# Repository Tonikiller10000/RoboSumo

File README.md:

# RoboSumo

## Description:

This is a SUMO robot for comperitions. It pushes the opponent\`s robot out of the ring.
    
It uses:
- ATmega328p-AU as an microcontroller(used in arduino uno);
- 16 or 20Mhz crystal resonator;
- [TB6612FNG](https://github.com/Tonikiller10000/MotorDriver_1) DC motor driver;
- [VL53L0x](https://github.com/Tonikiller10000/VL53L0x_DistanceSensor) distance sensor;
- LI-PO battery (7.2V)
- 2x DC motors with low torque high speed gear box
- robot suport (Wood, 3d printed or any low weight matherial)

<table>
  <tr>
    <td></td>
    <td></td>
    <td></td>
  </tr>
</table>

Schematic:

### How it works:
The board is like a custom arduino UNO board powered from an 7.2V Li-Po battery trouth an 5V voltage regulator. 6 digital pins are used for the TB6612FNG motor driver witch is powered dirrectly from the battery to give more power to the motors. The reset pin has a 10K pullup resistor witch is pulled down by the reset button when it is pressed. The UART and ICSP pins wore pulled out to program the code and the bootloader of the IC.
For now I will try to use the [VL53L0x](https://github.com/Tonikiller10000/VL53L0x_DistanceSensor) I2C distance sensor, because [other sensors](https://github.com/Tonikiller10000/RoboSumo/blob/main/PozeRoboSumo/s1.png) are a little to slow.

### Programming:
Programming of the robot is done via UART protocoll with an [FTDI](https://github.com/Tonikiller10000/CH340G-FTDI-PROGRAMER) programming board. The code for the RoboSumo is not ready. 
 
### Design and mentions

This is The model I followed and some tips:
- to reach better torque on the wheels, it should be wider. 
- to mount the motors use molderd plastic motor holders, or be carefull when printing [it](https://github.com/Tonikiller10000/LineFollower/blob/main/LineFollower_Pictures/w1.jpg). 
- the case was made with autodesk fusion 360 at the 3d printer and with some M3 screws.

<table>
  <tr>
    <td></td>
    <td></td>
    <td></td>
  </tr>
</table>

The next version will have the motor driver soldered on the board and motors screwed dirrectly to it as the suport. Also I will try to make a smaller version

## Links: 
- ATmega328p-AU (microcontroller): 
- LM78L05 (5V voltage regulator):

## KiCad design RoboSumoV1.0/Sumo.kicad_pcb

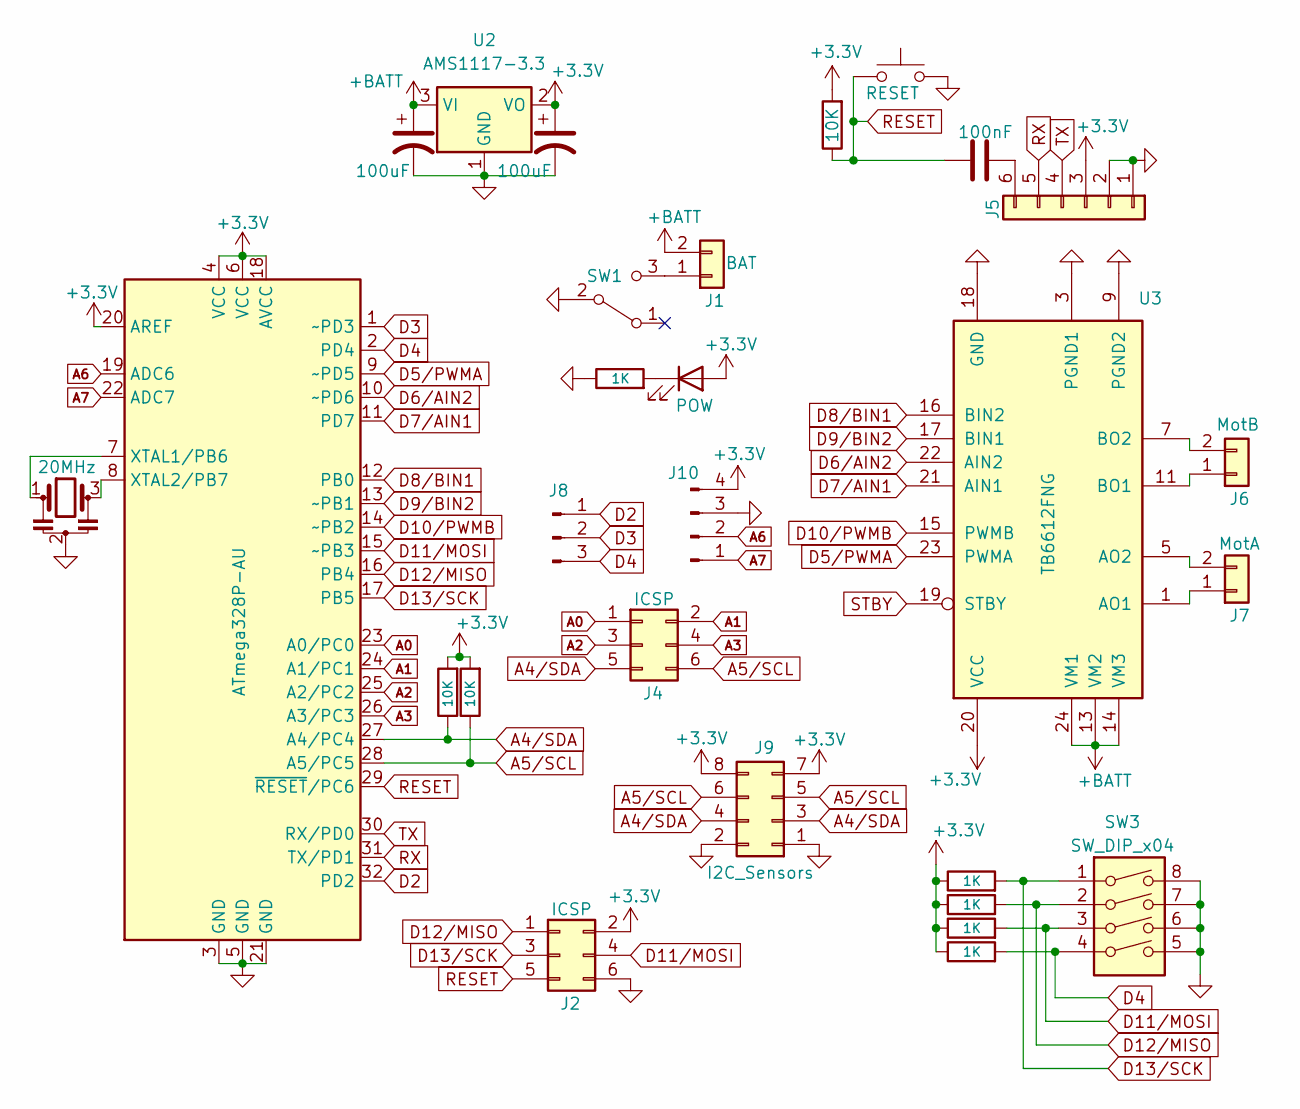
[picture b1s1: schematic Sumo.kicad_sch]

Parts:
C1, C2: 100uF; C_1210_3225Metric_Pad1.33x2.70mm_HandSolder
C3: 100nF; C_0805_2012Metric
D1: POW
J1: BAT; PinHeader_1x02_P2.54mm_Vertical
J2, J4: ICSP; PinHeader_2x03_P2.54mm_Vertical
J5: Conn_01x06_MountingPin
J6: MotB; PinHeader_1x02_P2.54mm_Horizontal
J7: MotA; PinHeader_1x02_P2.54mm_Horizontal
J8: Conn_01x03_Pin
J9: I2C_Sensors
J10: Conn_01x04_Pin
R1, R7, R8, R9, R10: 1K; R_1206_3216Metric
R2, R11, R12: 10K; R_1206_3216Metric
SW1: SW_SPDT
SW2: RESET
SW3: SW_DIP_x04
U1: ATmega328P-AU; TQFP-32_7x7mm_P0.8mm
U2: AMS1117-3.3; SOT-223-3_TabPin2
U3: TB6612FNG; SSOP-24_5.3x8.2mm_P0.65mm
Y1: 20MHz; Resonator_SMD_Murata_CSTxExxV-3Pin_3.0x1.1mm

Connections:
+5V: C2.1, D1.2 (A), J2.2, J5.3, J9.7, J9.8, J10.4, R2.2, R7.1, R8.1, R9.1, R10.1, R11.2, R12.2, U1.4 (VCC), U1.6 (VCC), U1.18 (AVCC), U1.20 (AREF), U2.2 (VO); also elsewhere on the board
+BATT: C1.1, J1.2, U2.3 (VI); also elsewhere on the board
A0: J4.1, U1.23 (A0/PC0)
A1: J4.2, U1.24 (A1/PC1)
A2: J4.3, U1.25 (A2/PC2)
A3: J4.4, U1.26 (A3/PC3)
A4/SDA: J4.5, J9.3, J9.4, R11.1, U1.27 (A4/PC4)
A5/SCL: J4.6, J9.5, J9.6, R12.1, U1.28 (A5/PC5)
A6: J10.2, U1.19 (ADC6)
A7: J10.1, U1.22 (ADC7)
D2: J8.1, U1.32 (PD2)
D3: J8.2, U1.1 (~PD3)
D4: J8.3, R10.2, SW3.4, U1.2 (PD4)
D5/PWMA: U1.9 (~PD5), U3.23 (PWMA); also elsewhere on the board
D6/AIN2: U1.10 (~PD6), U3.22 (AIN2); also elsewhere on the board
D7/AIN1: U1.11 (PD7), U3.21 (AIN1); also elsewhere on the board
D8/BIN1: U1.12 (PB0), U3.16 (BIN2); also elsewhere on the board
D9/BIN2: U1.13 (~PB1), U3.17 (BIN1); also elsewhere on the board
D10/PWMB: U1.14 (~PB2), U3.15 (PWMB); also elsewhere on the board
D11/MOSI: J2.4, R9.2, SW3.3, U1.15 (~PB3)
D12/MISO: J2.1, R8.2, SW3.2, U1.16 (PB4)
D13/SCK: J2.3, R7.2, SW3.1, U1.17 (PB5)
GND: C1.2, C2.2, J2.6, J5.1, J5.2, J9.1, J9.2, J10.3, R1.1, SW1.2 (B), SW2.1, SW3.5, SW3.6, SW3.7, SW3.8, U1.3 (GND), U1.5 (GND), U1.21 (GND), U2.1 (GND), Y1.2; also elsewhere on the board
unnamed: D1.1 (K), R1.2
unnamed: J1.1, SW1.3 (C)
unnamed: C3.1, J5.6
unnamed 26: J6.1; also elsewhere on the board
unnamed 27: J6.2; also elsewhere on the board
unnamed 28: J7.1; also elsewhere on the board
unnamed 29: J7.2; also elsewhere on the board
unnamed: U1.7 (XTAL1/PB6), Y1.1
unnamed: U1.8 (XTAL2/PB7), Y1.3
RESET: C3.2, J2.5, R2.1, SW2.2, U1.29 (~RESET/PC6)
RX: J5.5, U1.31 (TX/PD1)
TX: J5.4, U1.30 (RX/PD0)

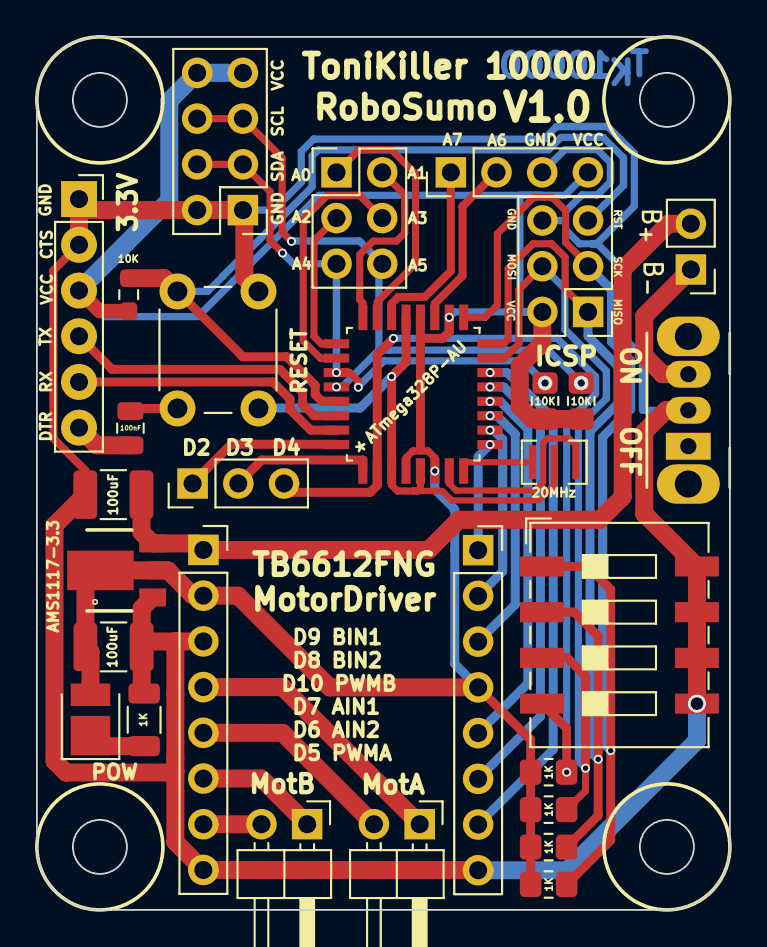
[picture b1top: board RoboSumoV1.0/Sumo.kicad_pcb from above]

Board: 2 copper layers, 38.5 x 48.5 mm, 29 parts (0 on the bottom side), 35 nets.

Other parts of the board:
J20: BAT; PinSocket_1x08_P2.54mm_Vertical
J21: Conn_01x03; PinSocket_1x08_P2.54mm_Vertical

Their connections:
+5V: J20.2, J21.4; also elsewhere on the board
+BATT: J20.1; also elsewhere on the board
D5/PWMA: J21.1; also elsewhere on the board
D6/AIN2: J21.2; also elsewhere on the board
D7/AIN1: J21.3; also elsewhere on the board
D8/BIN1: J21.5; also elsewhere on the board
D9/BIN2: J21.6; also elsewhere on the board
D10/PWMB: J21.7; also elsewhere on the board
GND: J20.3, J20.8, J21.8; also elsewhere on the board
unnamed 26: J20.6; also elsewhere on the board
unnamed 27: J20.7; also elsewhere on the board
unnamed 28: J20.4; also elsewhere on the board
unnamed 29: J20.5; also elsewhere on the board

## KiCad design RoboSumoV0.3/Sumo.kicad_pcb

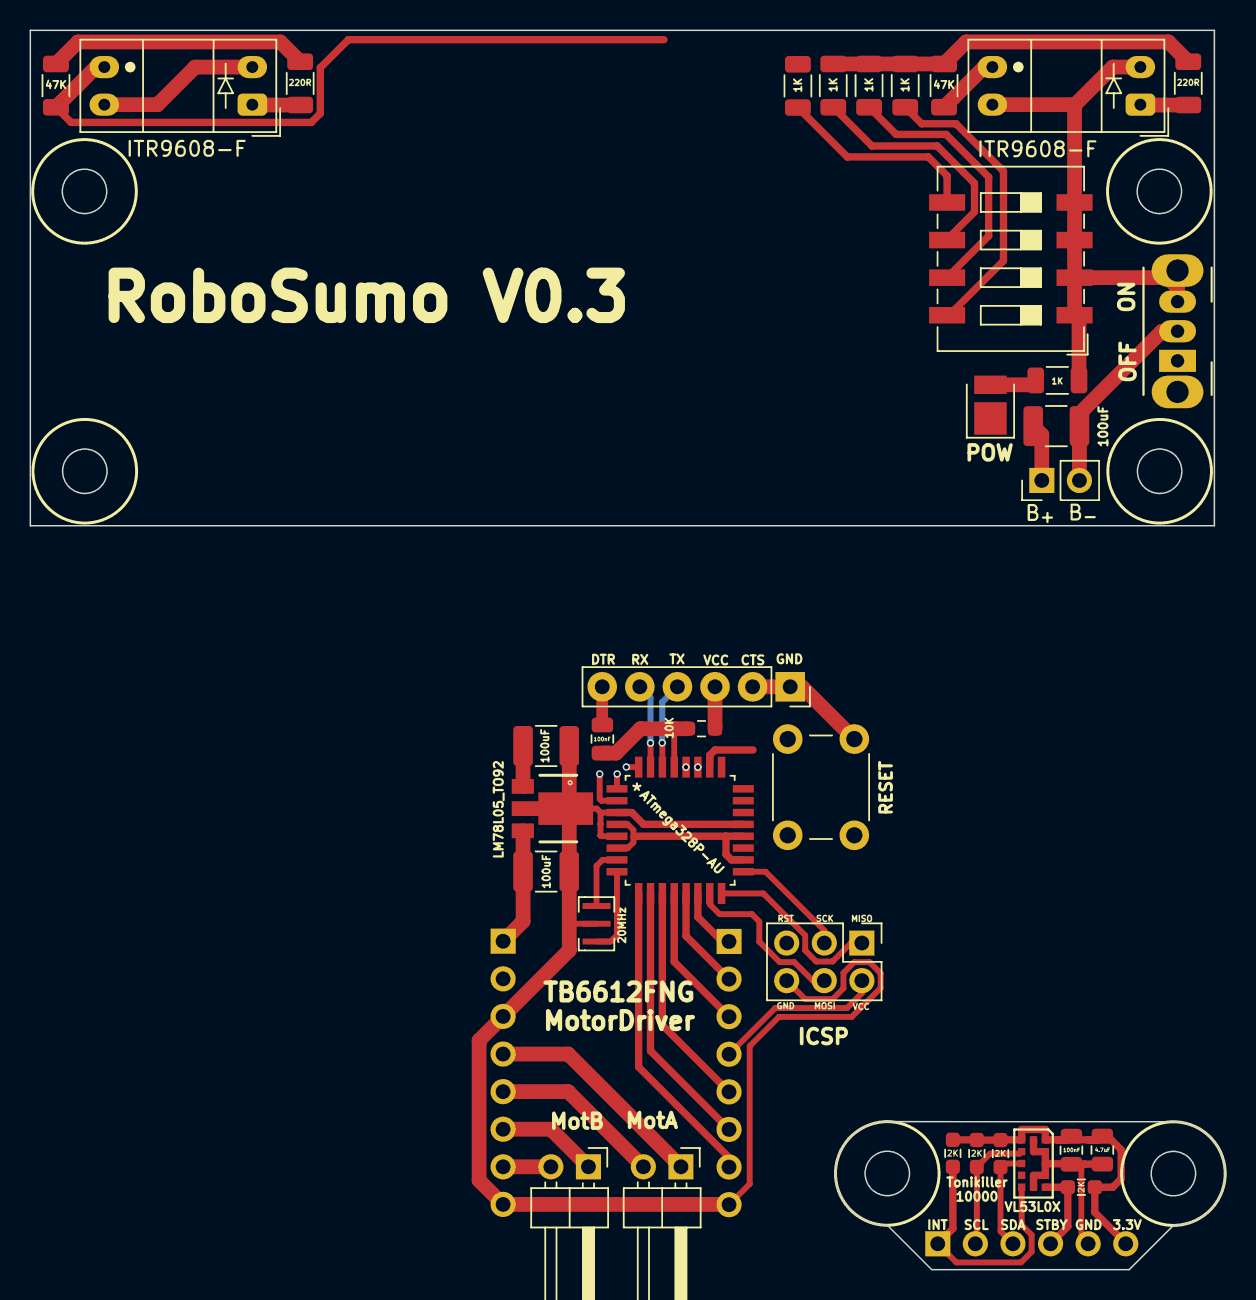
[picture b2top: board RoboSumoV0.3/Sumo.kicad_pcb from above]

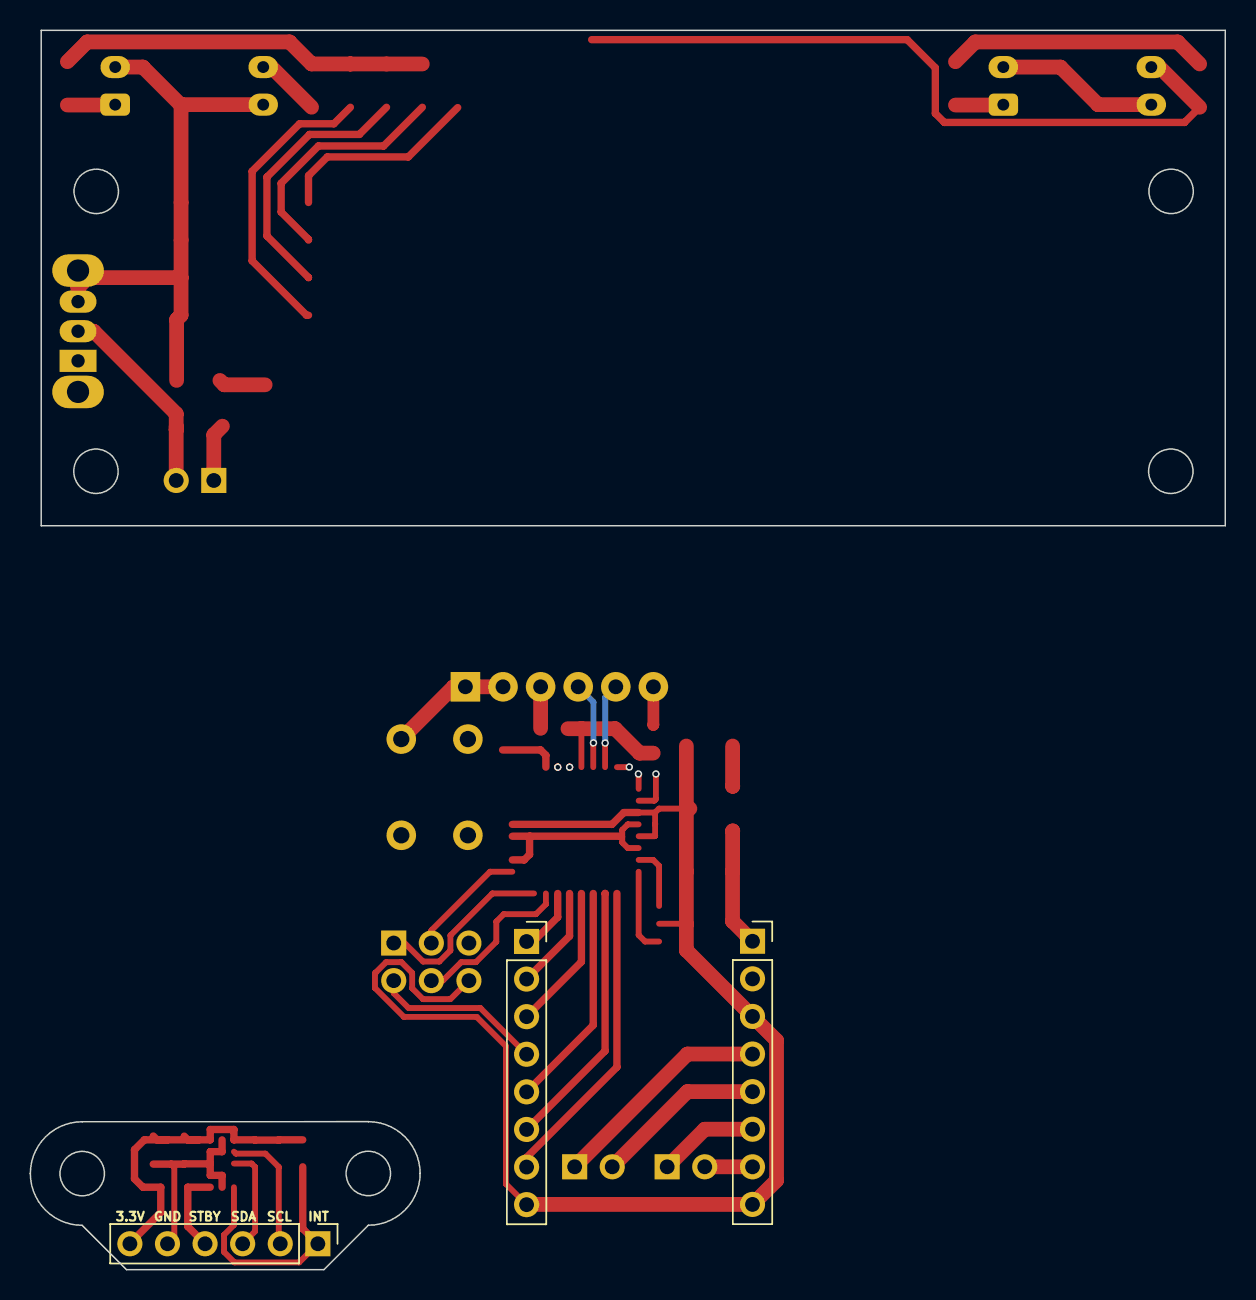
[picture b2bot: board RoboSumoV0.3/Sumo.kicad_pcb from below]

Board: 2 copper layers, 80.7 x 83.7 mm, 35 parts (2 on the bottom side), 27 nets.

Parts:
C1, C1#2, C2: 100uF; C_1210_3225Metric_Pad1.33x2.70mm_HandSolder
C3, C3#2: 100nF; C_0805_2012Metric
C3#3: 4.7uF; C_0805_2012Metric
D1: POW; LED_PLCC_2835
J1: BAT; PinHeader_1x02_P2.54mm_Vertical
J2: ICSP; PinHeader_2x03_P2.54mm_Vertical
J4: Conn_01x06_MountingPin; PinSocket_1x06_P2.54mm_Vertical
J6: MotB; PinHeader_1x02_P2.54mm_Horizontal
J7: MotA; PinHeader_1x02_P2.54mm_Horizontal
J8: BAT; PinSocket_1x08_P2.54mm_Vertical
J9: Conn_01x03; PinSocket_1x08_P2.54mm_Vertical
R1: 10K; R_0603_1608Metric_Pad0.98x0.95mm_HandSolder
R1#2, R1#3, R1#4, R1#5: 2K; R_0603_1608Metric_Pad0.98x0.95mm_HandSolder
R2, R20, R20#2, R20#3, R20#4: 1K; R_1206_3216Metric
R3, R5: 220R; R_1206_3216Metric
R4, R6: 47K; R_1206_3216Metric
SW1: RESET; SW_CuK_OS102011MA1QN1_SPDT_Angled
SW2: RESET; SW_PUSH_6mm
U1: ATmega328P-AU; TQFP32_32A_MCH
U2: LM78L05_TO92; PK(R-PSSO-F3)
U4, U5: ITR9608-F; Everlight_ITR9608-F
Y1: 20MHz; Resonator_SMD_Murata_CSTxExxV-3Pin_3.0x1.1mm

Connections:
0V: C1#2.2, C2.2, D1.1 (K), J2.6, J4.1, J4.2, J8.3, J8.8, J9.8, R2.2, SW1.3, SW2.2, U1.3 (GND), U1.5 (GND), U1.21 (GND), U2.2 (GND), U4.2, U4.4, U5.2, U5.4, Y1.2
5V: C2.1, J2.2, J4.3, J9.4, R3.2, R4.1, R5.2, R6.1, R20.1, R20#2.1, R20#3.1, R20#4.1, U1.4 (VCC), U1.6 (VCC), U1.18 (AVCC), U1.20 (AREF), U2.1 (VO)
+BATT: C1.1, C1#2.1, J1.1, J8.1, U2.3 (VI)
AIN1: J9.3, U1.12 (PB0), U1.32 (PD2)
AIN2: J9.2, U1.2 (PD4), U1.13 (~PB1)
BIN1: J9.5, U1.11 (PD7)
BIN2: J9.6, U1.10 (~PD6)
MISO: J2.1, U1.16 (PB4)
MOSI: J2.4, U1.15 (~PB3)
unnamed: D1.2 (A), R2.1
unnamed: C1.2, J1.2, SW1.2
unnamed: J6.1, J8.6
unnamed: J6.x (Pin_2), J8.7
unnamed: J7.1, J8.4
unnamed: J7.2, J8.5
unnamed: R3.1, U4.1
unnamed: R5.1, U5.1
unnamed: U1.7 (XTAL1/PB6), Y1.1
unnamed: U1.8 (XTAL2/PB7), Y1.3
PWMA: J9.1, U1.1 (~PD3), U1.14 (~PB2)
PWMB: J9.7, U1.9 (~PD5)
RESET: C3.2, J2.5, R1.1, SW2.1, U1.29 (~RESET/PC6)
RX: J4.5, U1.31 (TX/PD1)
SCK: J2.3, U1.17 (PB5)
Sensor4: R6.2, U1.27 (A4/PC4), U5.3
Sensor5: R4.2, U1.28 (A5/PC5), U4.3
TX: J4.4, U1.30 (RX/PD0)

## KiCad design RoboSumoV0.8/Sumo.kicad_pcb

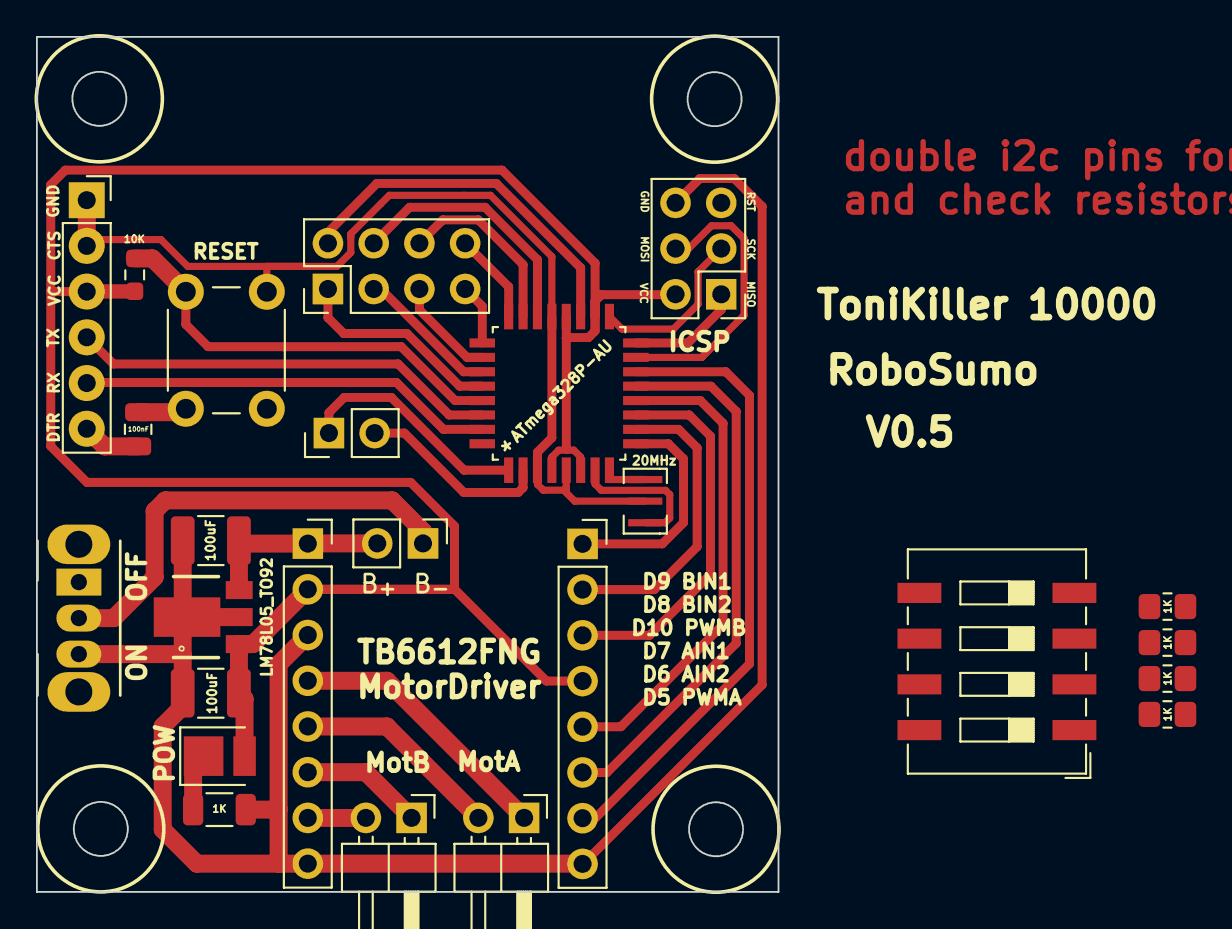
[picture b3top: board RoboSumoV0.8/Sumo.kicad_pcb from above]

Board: 2 copper layers, 41.2 x 47.5 mm, 24 parts (0 on the bottom side), 27 nets.

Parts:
C1, C2: 100uF; C_1210_3225Metric_Pad1.33x2.70mm_HandSolder
C3: 100nF; C_0805_2012Metric
D1: POW; LED_PLCC_2835
J1, J1#2: BAT; PinHeader_1x02_P2.54mm_Vertical
J2: ICSP; PinHeader_2x03_P2.54mm_Vertical
J5: Conn_01x06_MountingPin; PinSocket_1x06_P2.54mm_Vertical
J6: MotB; PinHeader_1x02_P2.54mm_Horizontal
J7: MotA; PinHeader_1x02_P2.54mm_Horizontal
J8: BAT; PinSocket_1x08_P2.54mm_Vertical
J9: Conn_01x03; PinSocket_1x08_P2.54mm_Vertical
R1: 1K; R_1206_3216Metric
R2: 10K; R_0603_1608Metric_Pad0.98x0.95mm_HandSolder
R7, R8, R9, R10: 1K; R_0805_2012Metric_Pad1.20x1.40mm_HandSolder
SW1: SW_SPDT; SW_CuK_OS102011MA1QN1_SPDT_Angled
SW2: RESET; SW_PUSH_6mm
SW3: SW_DIP_x04; SW_DIP_SPSTx04_Slide_9.78x12.34mm_W8.61mm_P2.54mm
U1: ATmega328P-AU; TQFP32_32A_MCH
U2: LM78L05_TO92; PK(R-PSSO-F3)
Y1: 20MHz; Resonator_SMD_Murata_CSTxExxV-3Pin_3.0x1.1mm

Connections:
+5V: C2.1, D1.2 (A), J2.2, J5.3, J8.2, J9.4, R2.2, R7.1, R8.1, R9.1, R10.1, U1.4 (VCC), U1.6 (VCC), U1.18 (AVCC), U1.20 (AREF), U2.1 (VO)
+BATT: C1.1, J1#2.2, J8.1, U2.3 (VI)
AIN1: J9.3, U1.11 (PD7)
AIN2: J9.2, U1.10 (~PD6)
BIN1: J9.5, U1.12 (PB0)
BIN2: J9.6, U1.13 (~PB1)
DTR: C3.1, J5.6
GND: C1.2, C2.2, J2.6, J5.1, J5.2, J8.3, J8.8, J9.8, R1.1, SW1.3 (C), SW2.1, SW3.5, SW3.6, SW3.7, SW3.8, U1.3 (GND), U1.5 (GND), U1.21 (GND), U2.2 (GND), Y1.2
MISO: J2.1, U1.16 (PB4)
MOSI: J2.4, U1.15 (~PB3)
unnamed: D1.1 (K), R1.2
unnamed: J1#2.1, SW1.2 (B)
unnamed: J6.1, J8.6
unnamed: J7.1, J8.4
unnamed: J7.2, J8.5
unnamed: R7.2, SW3.1
unnamed: R8.2, SW3.2
unnamed: R9.2, SW3.3
unnamed: R10.2, SW3.4
unnamed: U1.7 (XTAL1/PB6), Y1.1
unnamed: U1.8 (XTAL2/PB7), Y1.3
PWMA: J9.1, U1.9 (~PD5)
PWMB: J9.7, U1.14 (~PB2)
RESET: C3.2, J2.5, R2.1, SW2.2, U1.29 (~RESET/PC6)
RX: J5.5, U1.31 (TX/PD1)
SCK: J2.3, U1.17 (PB5)
TX: J5.4, U1.30 (RX/PD0)

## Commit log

2024-03-12 init

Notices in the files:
parts and their libraries:
Copyright 2021 Accelerated Designs. All rights reserved.
